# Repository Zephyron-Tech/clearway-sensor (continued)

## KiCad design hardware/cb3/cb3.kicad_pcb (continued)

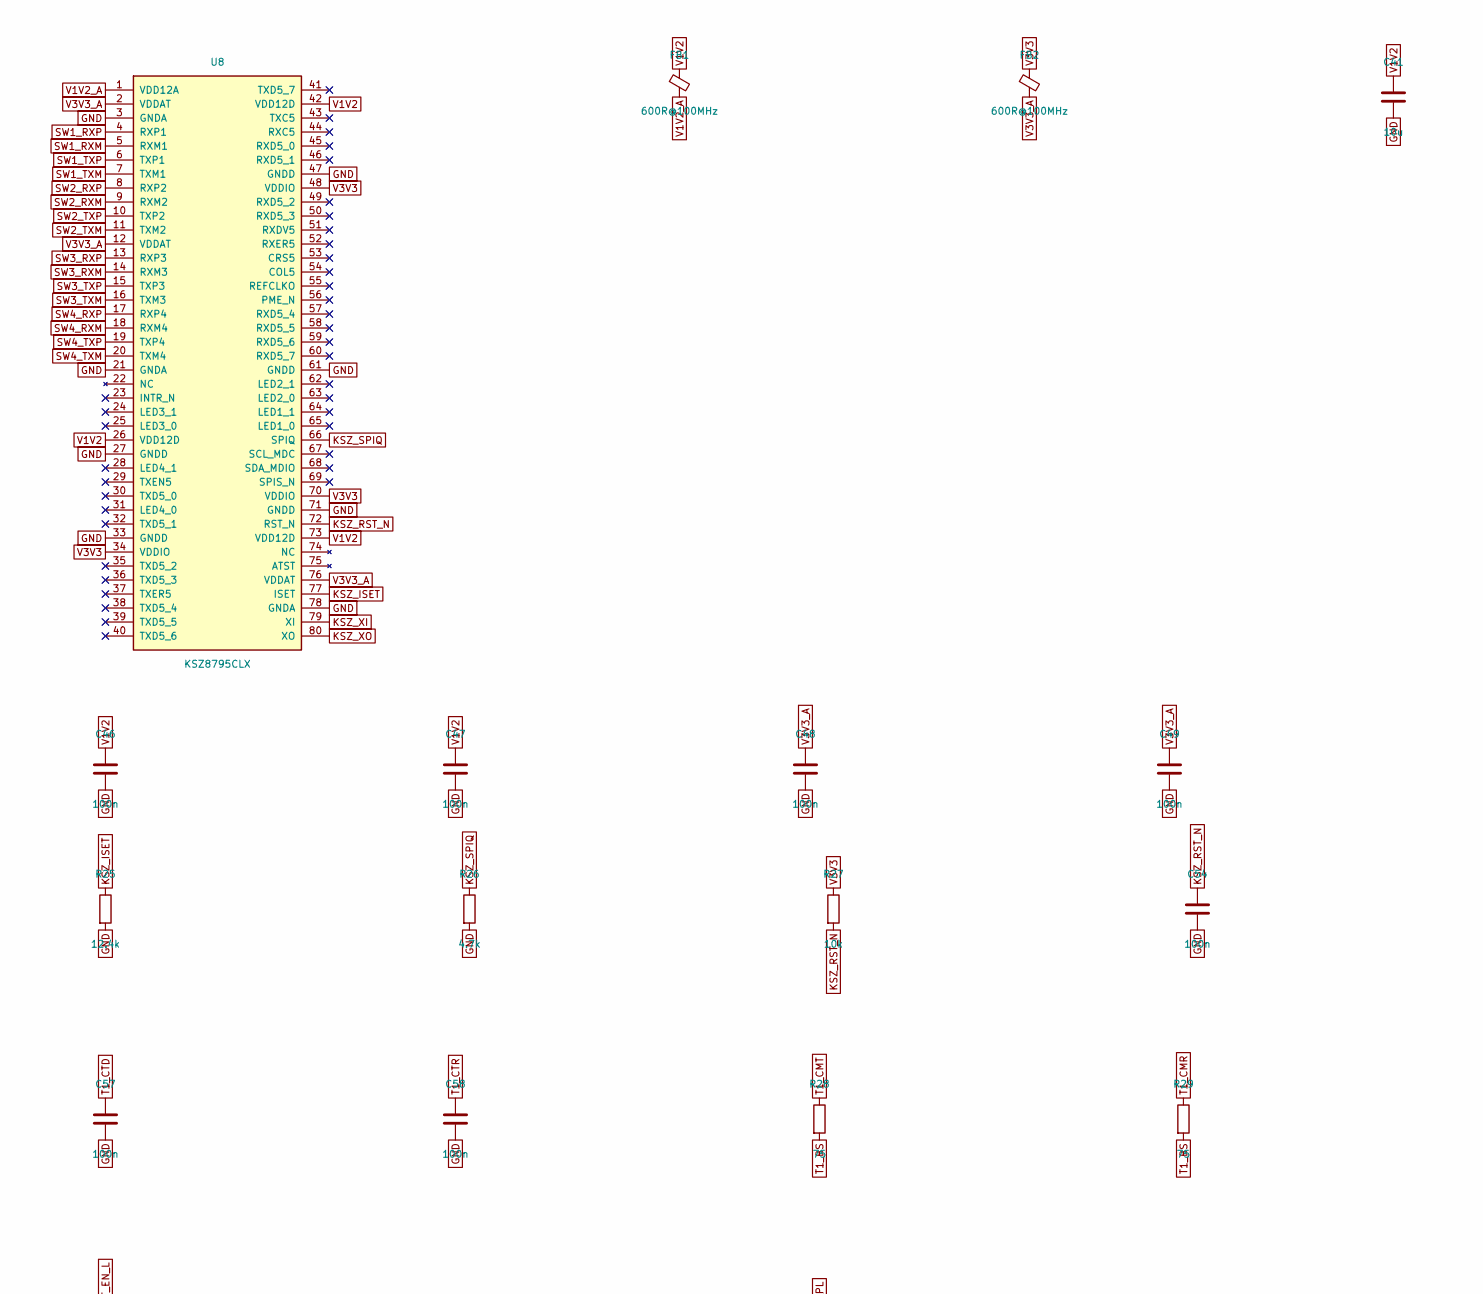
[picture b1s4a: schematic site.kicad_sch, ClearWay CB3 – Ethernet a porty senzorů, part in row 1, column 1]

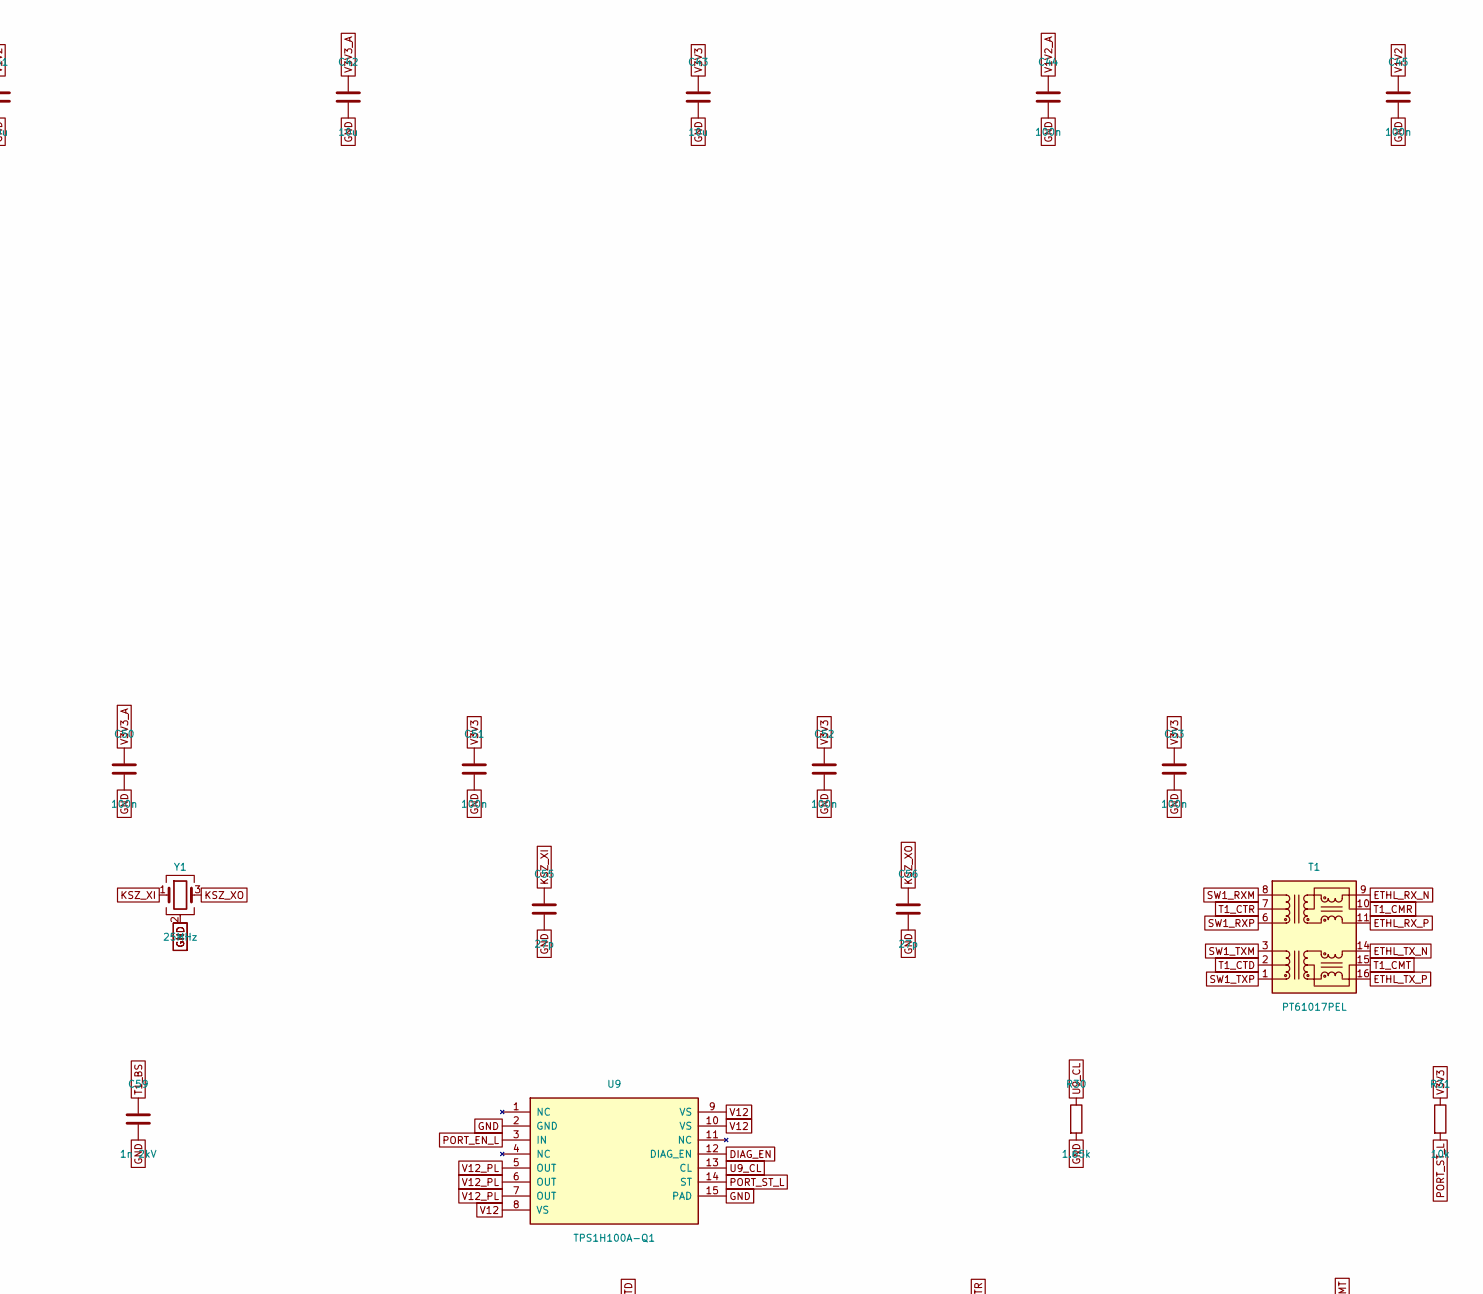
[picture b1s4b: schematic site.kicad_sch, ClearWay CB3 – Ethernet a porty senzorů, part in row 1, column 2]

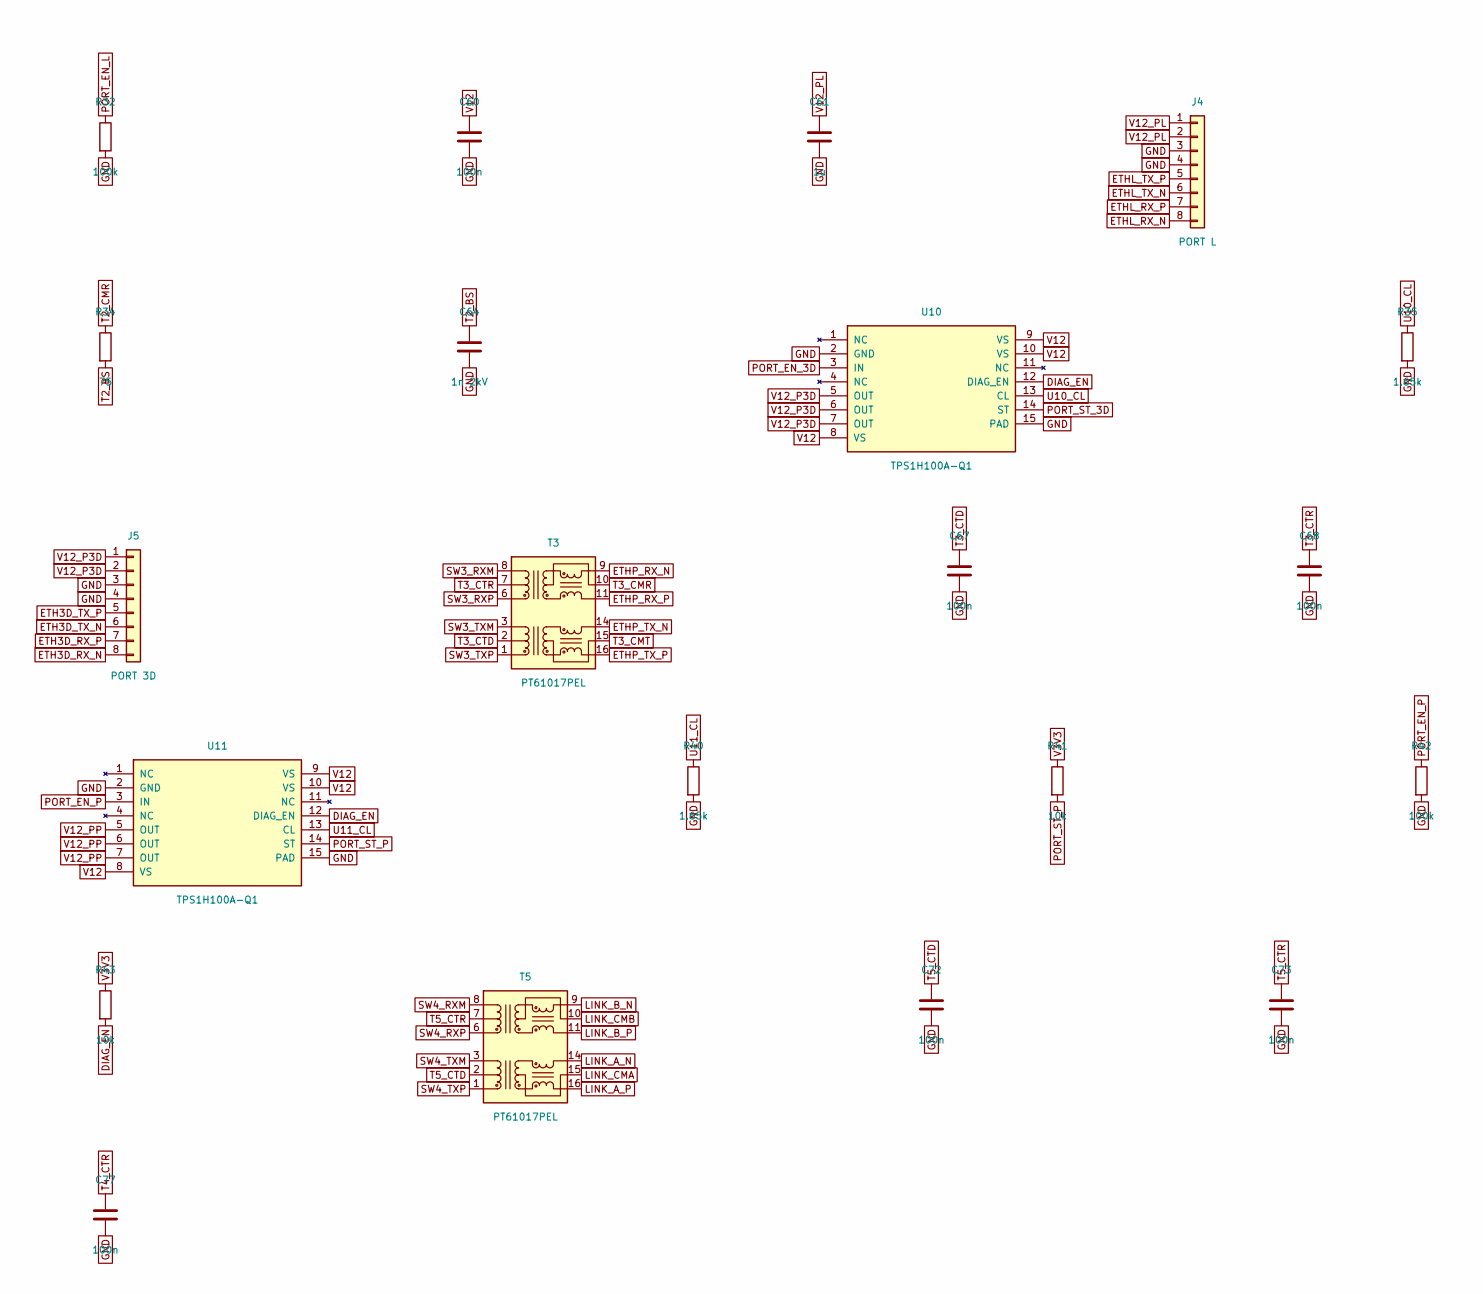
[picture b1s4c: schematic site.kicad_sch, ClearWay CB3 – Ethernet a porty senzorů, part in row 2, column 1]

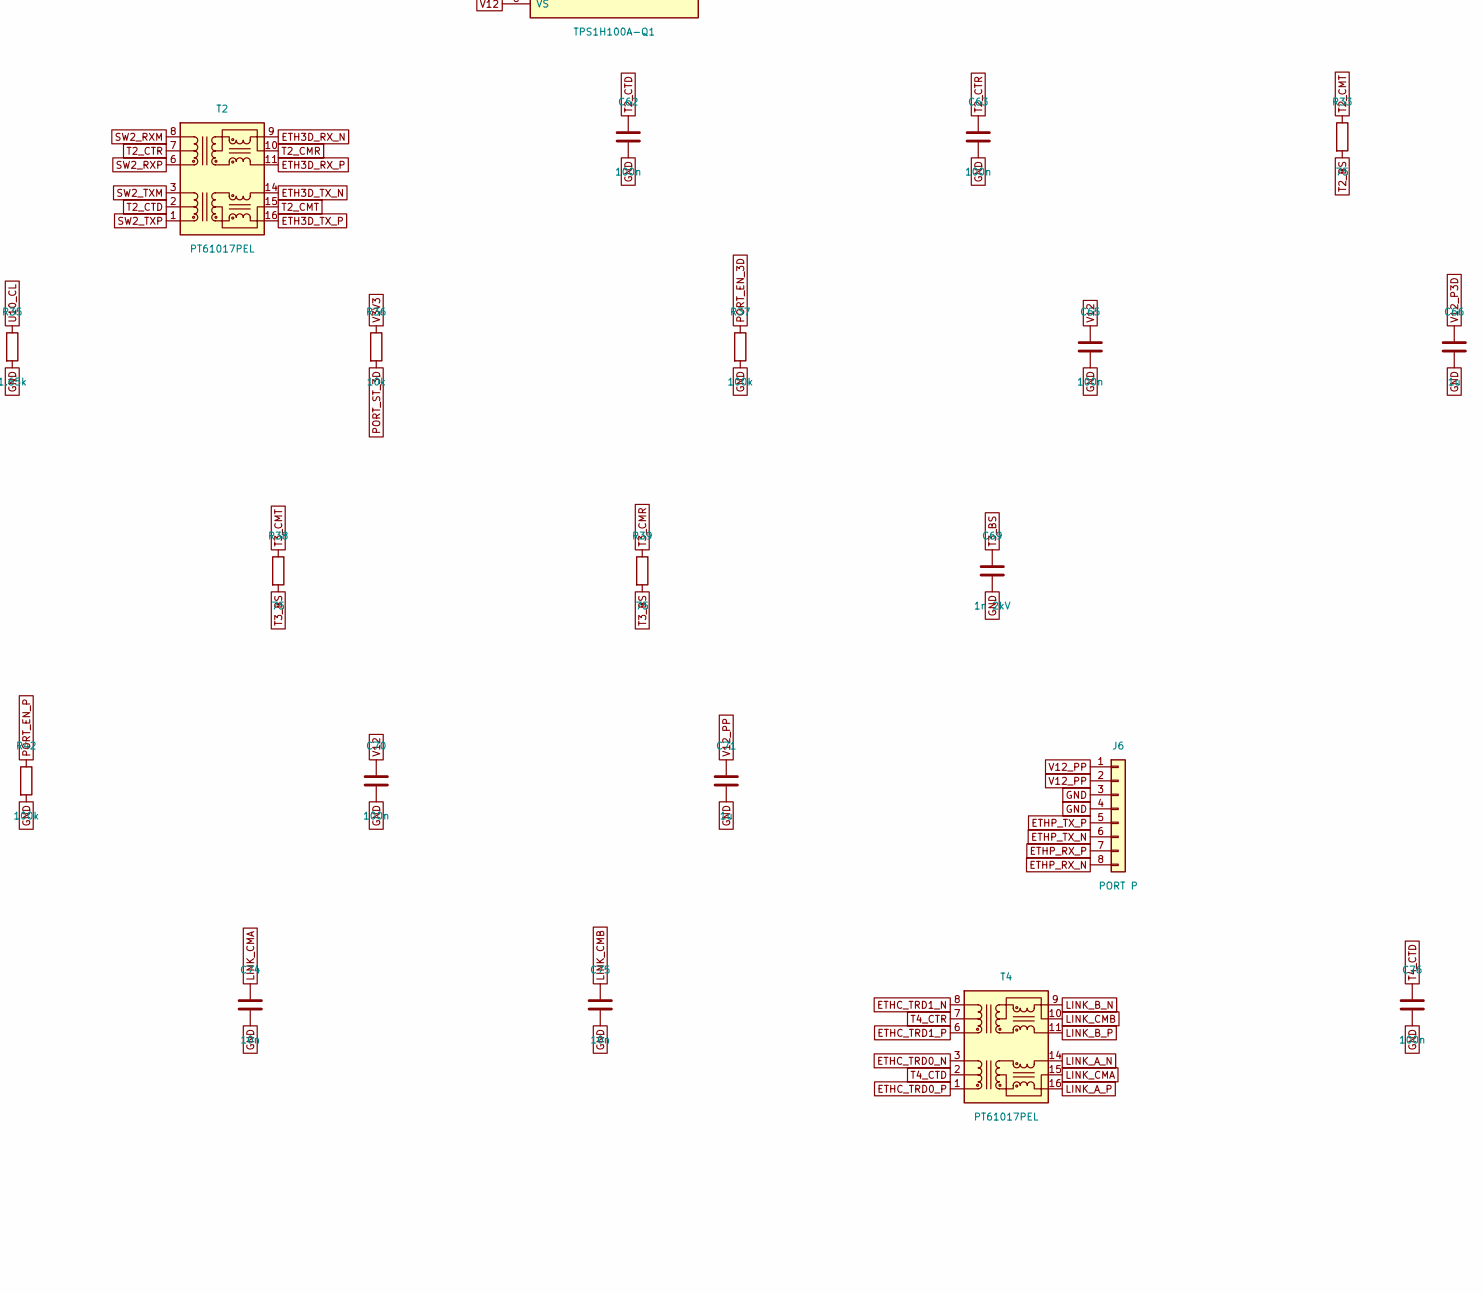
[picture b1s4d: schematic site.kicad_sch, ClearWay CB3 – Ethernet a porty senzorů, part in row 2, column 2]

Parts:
C41, C42, C43: 10u; C_0805_2012Metric; MPN kondenzátor 10 µF 10 V X5R 0805
C44, C45, C46, C47, C48, C49, C50, C51, C52, C53, C54, C57, C58, C62, C63, C67, C68, C72, C73, C76, C77: 100n; C_0402_1005Metric; MPN keramický kondenzátor 100n X7R
C55, C56: 27p; C_0402_1005Metric; MPN kondenzátor 27 pF C0G
C59, C64, C69: 1n 2kV; C_1206_3216Metric; MPN kondenzátor 1 nF 2 kV X7R 1206
C60, C65, C70: 100n; C_0603_1608Metric; MPN kondenzátor 100 nF 50 V X7R 0603
C61, C66, C71: 1u; C_0805_2012Metric; MPN kondenzátor 1 µF 50 V X7R 0805
C74, C75: 10n; C_0402_1005Metric; MPN keramický kondenzátor 10n X7R
FB1, FB2: 600R@100MHz; L_0603_1608Metric; MPN Murata BLM18PG601SN1D
J4: PORT L; JST_GH_SM08B-GHS-TB_1x08-1MP_P1.25mm_Horizontal; MPN JST SM08B-GHS-TB
J5: PORT 3D; JST_GH_SM08B-GHS-TB_1x08-1MP_P1.25mm_Horizontal; MPN JST SM08B-GHS-TB
J6: PORT P; JST_GH_SM08B-GHS-TB_1x08-1MP_P1.25mm_Horizontal; MPN JST SM08B-GHS-TB
R25: 12.4k; R_0402_1005Metric; MPN rezistor 12,4 kΩ 1 % 0402 (ISET)
R26: 4.7k; R_0402_1005Metric; MPN rezistor 4,7 kΩ 0402 (strap: SPI klient)
R27, R31, R36, R41, R43: 10k; R_0402_1005Metric; MPN rezistor 10k 1 % 0402
R28, R29, R33, R34, R38, R39: 75; R_0402_1005Metric; MPN rezistor 75 1 % 0402
R30, R35, R40: 1.65k; R_0402_1005Metric; MPN rezistor 1,65 kΩ 1 % 0402 (omezení prou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
R32, R37, R42: 100k; R_0402_1005Metric; MPN rezistor 100k 1 % 0402
T1, T2, T3, T4, T5: PT61017PEL; Transformer_Ethernet_Bourns_PT61017PEL; MPN Bourns PT61017PEL (10/100, 1:1)
U8: KSZ8795CLX; LQFP-80_12x12mm_P0.5mm; MPN Microchip KSZ8795CLXIC
U9, U10, U11: TPS1H100A-Q1; TSSOP-14-1EP_4.4x5mm_P0.65mm; MPN TI TPS1H100AQPWPRQ1 (verze A, výstup ST)
Y1: 25MHz; Crystal_SMD_3225-4Pin_3.2x2.5mm; MPN Abracon ABM8-25.000MHZ-B2-T (18 pF, ±30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

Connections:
DIAG_EN: R43.2, U9.12 (DIAG_EN), U10.12 (DIAG_EN), U11.12 (DIAG_EN)
ETH3D_RX_N: J5.8, T2.9 (RX-)
ETH3D_RX_P: J5.7, T2.11 (RX+)
ETH3D_TX_N: J5.6, T2.14 (TX-)
ETH3D_TX_P: J5.5, T2.16 (TX+)
ETHC_TRD0_N: T4.3 (TD-); also elsewhere on the board
ETHC_TRD0_P: T4.1 (TD+); also elsewhere on the board
ETHC_TRD1_N: T4.8 (RD-); also elsewhere on the board
ETHC_TRD1_P: T4.6 (RD+); also elsewhere on the board
ETHL_RX_N: J4.8, T1.9 (RX-)
ETHL_RX_P: J4.7, T1.11 (RX+)
ETHL_TX_N: J4.6, T1.14 (TX-)
ETHL_TX_P: J4.5, T1.16 (TX+)
ETHP_RX_N: J6.8, T3.9 (RX-)
ETHP_RX_P: J6.7, T3.11 (RX+)
ETHP_TX_N: J6.6, T3.14 (TX-)
ETHP_TX_P: J6.5, T3.16 (TX+)
GND: C41.2, C42.2, C43.2, C44.2, C45.2, C46.2, C47.2, C48.2, C49.2, C50.2, C51.2, C52.2, C53.2, C54.2, C55.2, C56.2, C57.2, C58.2, C59.2, C60.2, C61.2, C62.2, C63.2, C64.2, C65.2, C66.2, C67.2, C68.2, C69.2, C70.2, C71.2, C72.2, C73.2, C74.2, C75.2, C76.2, C77.2, J4.3, J4.4, J4.MP, J5.3, J5.4, J5.MP, J6.3, J6.4, J6.MP, R25.2, R26.2, R30.2, R32.2, R35.2, R37.2, R40.2, R42.2, U8.3 (GNDA), U8.21 (GNDA), U8.27 (GNDD), U8.33 (GNDD), U8.47 (GNDD), U8.61 (GNDD), U8.71 (GNDD), U8.78 (GNDA), U9.2 (GND), U9.15 (PAD), U10.2 (GND), U10.15 (PAD), U11.2 (GND), U11.15 (PAD), Y1.2 (G), Y1.4 (G); also elsewhere on the board
KSZ_ISET: R25.1, U8.77 (ISET)
KSZ_RST_N: C54.1, R27.2, U8.72 (RST_N); also elsewhere on the board
KSZ_SPIQ: R26.1, U8.66 (SPIQ)
KSZ_XI: C55.1, U8.79 (XI), Y1.1
KSZ_XO: C56.1, U8.80 (XO), Y1.3
LINK_A_N: T4.14 (TX-), T5.14 (TX-)
LINK_A_P: T4.16 (TX+), T5.16 (TX+)
LINK_B_N: T4.9 (RX-), T5.9 (RX-)
LINK_B_P: T4.11 (RX+), T5.11 (RX+)
LINK_CMA: C74.1, T4.15 (C_TX), T5.15 (C_TX)
LINK_CMB: C75.1, T4.10 (C_RX), T5.10 (C_RX)
PORT_EN_3D: R37.1, U10.3 (IN); also elsewhere on the board
PORT_EN_L: R32.1, U9.3 (IN); also elsewhere on the board
PORT_EN_P: R42.1, U11.3 (IN); also elsewhere on the board
PORT_ST_3D: R36.2, U10.14 (ST); also elsewhere on the board
PORT_ST_L: R31.2, U9.14 (ST); also elsewhere on the board
PORT_ST_P: R41.2, U11.14 (ST); also elsewhere on the board
SW1_RXM: T1.8 (RD-), U8.5 (RXM1)
SW1_RXP: T1.6 (RD+), U8.4 (RXP1)
SW1_TXM: T1.3 (TD-), U8.7 (TXM1)
SW1_TXP: T1.1 (TD+), U8.6 (TXP1)
SW2_RXM: T2.8 (RD-), U8.9 (RXM2)
SW2_RXP: T2.6 (RD+), U8.8 (RXP2)
SW2_TXM: T2.3 (TD-), U8.11 (TXM2)
SW2_TXP: T2.1 (TD+), U8.10 (TXP2)
SW3_RXM: T3.8 (RD-), U8.14 (RXM3)
SW3_RXP: T3.6 (RD+), U8.13 (RXP3)
SW3_TXM: T3.3 (TD-), U8.16 (TXM3)
SW3_TXP: T3.1 (TD+), U8.15 (TXP3)
SW4_RXM: T5.8 (RD-), U8.18 (RXM4)
SW4_RXP: T5.6 (RD+), U8.17 (RXP4)
SW4_TXM: T5.3 (TD-), U8.20 (TXM4)
SW4_TXP: T5.1 (TD+), U8.19 (TXP4)
T1_BS: C59.1, R28.2, R29.2
T1_CMR: R29.1, T1.10 (C_RX)
T1_CMT: R28.1, T1.15 (C_TX)
T1_CTD: C57.1, T1.2 (C_TD)
T1_CTR: C58.1, T1.7 (C_RD)
T2_BS: C64.1, R33.2, R34.2
T2_CMR: R34.1, T2.10 (C_RX)
T2_CMT: R33.1, T2.15 (C_TX)
T2_CTD: C62.1, T2.2 (C_TD)
T2_CTR: C63.1, T2.7 (C_RD)
T3_BS: C69.1, R38.2, R39.2
T3_CMR: R39.1, T3.10 (C_RX)
T3_CMT: R38.1, T3.15 (C_TX)
T3_CTD: C67.1, T3.2 (C_TD)
T3_CTR: C68.1, T3.7 (C_RD)
T4_CTD: C76.1, T4.2 (C_TD)
T4_CTR: C77.1, T4.7 (C_RD)
T5_CTD: C72.1, T5.2 (C_TD)
T5_CTR: C73.1, T5.7 (C_RD)
U9_CL: R30.1, U9.13 (CL)
U10_CL: R35.1, U10.13 (CL)
U11_CL: R40.1, U11.13 (CL)
V1V2: C41.1, C45.1, C46.1, C47.1, FB1.1, U8.26 (VDD12D), U8.42 (VDD12D), U8.73 (VDD12D); also elsewhere on the board
V1V2_A: C44.1, FB1.2, U8.1 (VDD12A)
V3V3: C43.1, C51.1, C52.1, C53.1, FB2.1, R27.1, R31.1, R36.1, R41.1, R43.1, U8.34 (VDDIO), U8.48 (VDDIO), U8.70 (VDDIO); also elsewhere on the board
V3V3_A: C42.1, C48.1, C49.1, C50.1, FB2.2, U8.2 (VDDAT), U8.12 (VDDAT), U8.76 (VDDAT)
V12: C60.1, C65.1, C70.1, U9.8 (VS), U9.9 (VS), U9.10 (VS), U10.8 (VS), U10.9 (VS), U10.10 (VS), U11.8 (VS), U11.9 (VS), U11.10 (VS); also elsewhere on the board
V12_P3D: C66.1, J5.1, J5.2, U10.5 (OUT), U10.6 (OUT), U10.7 (OUT)
V12_PL: C61.1, J4.1, J4.2, U9.5 (OUT), U9.6 (OUT), U9.7 (OUT)
V12_PP: C71.1, J6.1, J6.2, U11.5 (OUT), U11.6 (OUT), U11.7 (OUT)

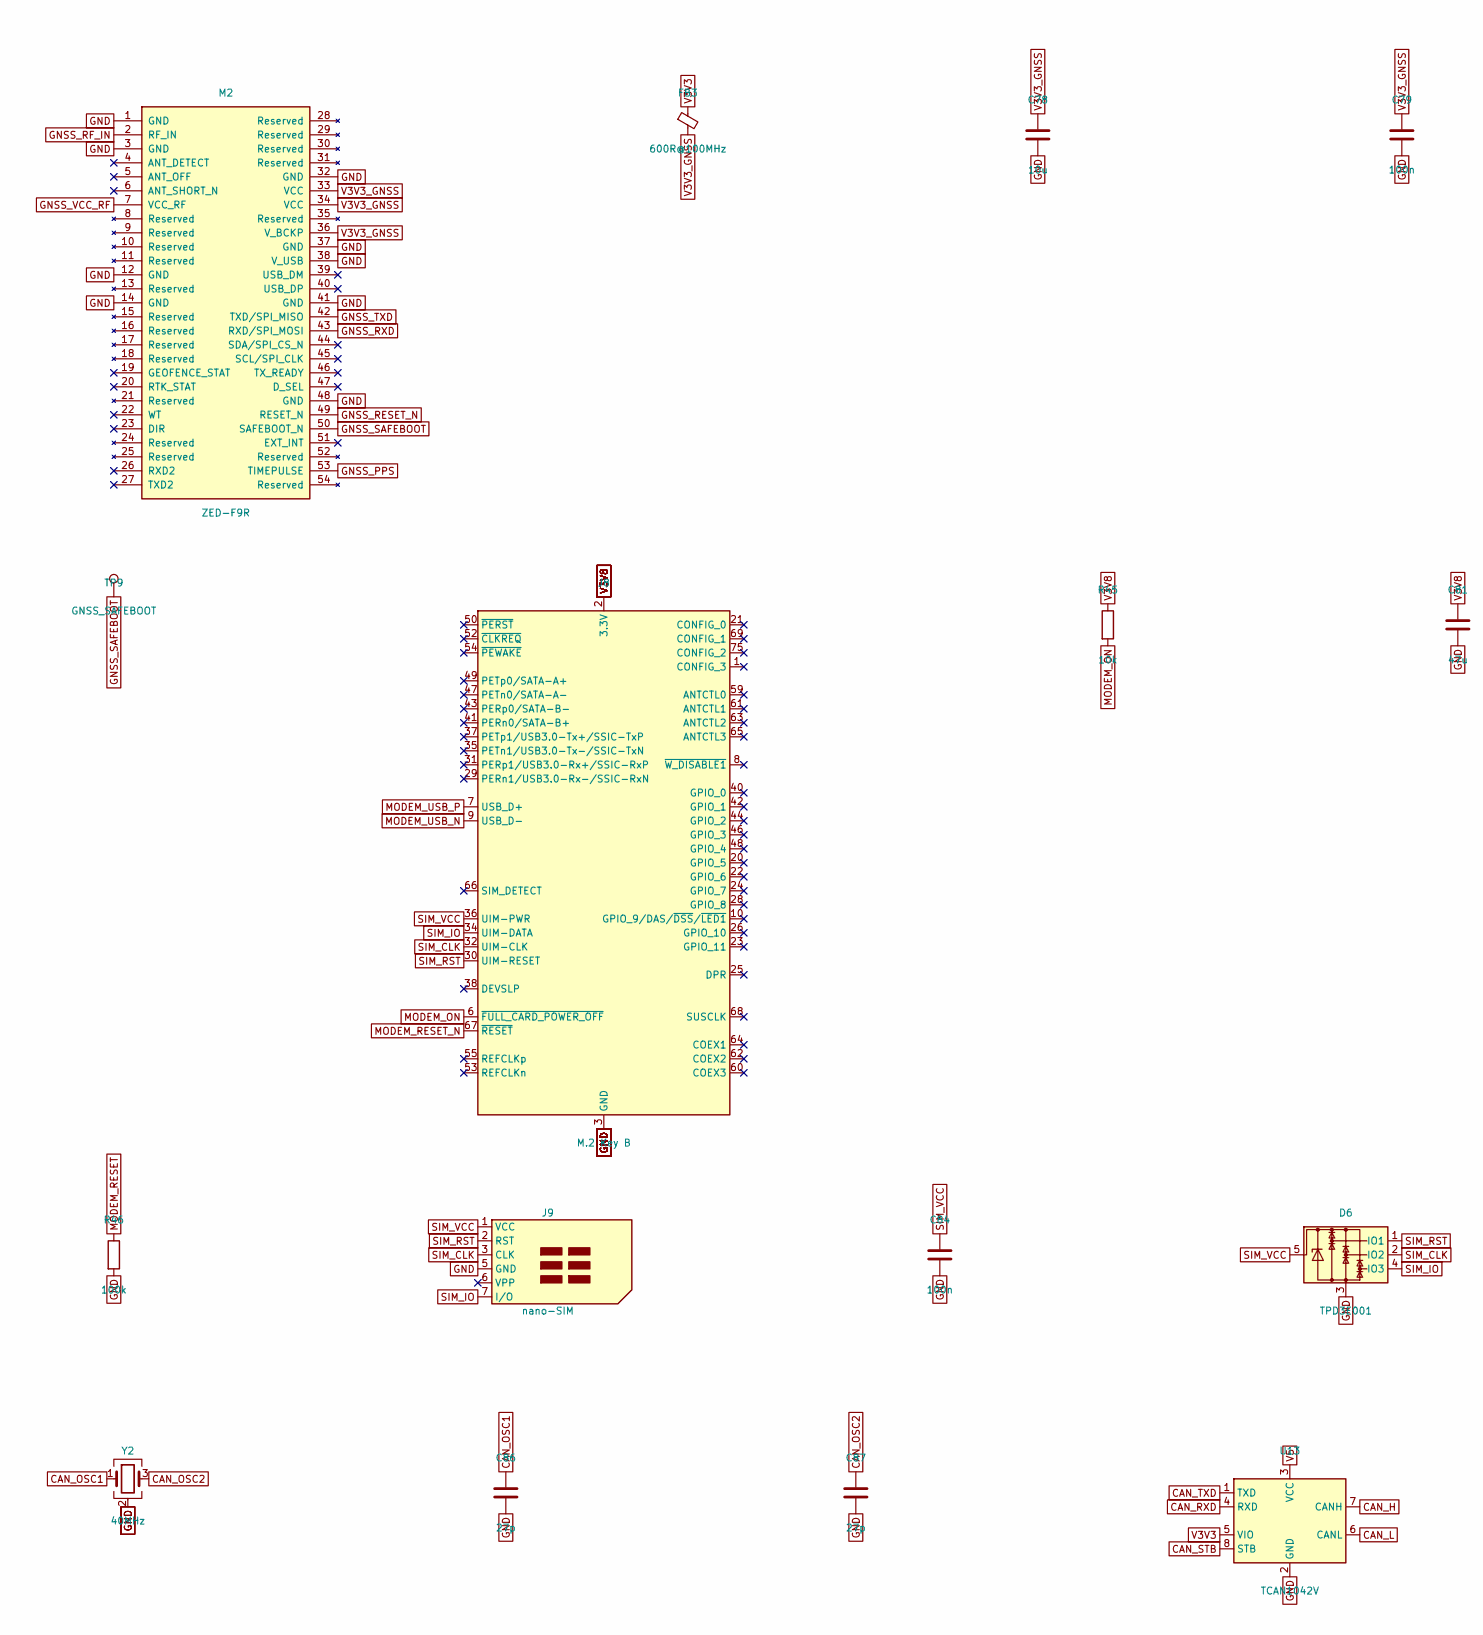
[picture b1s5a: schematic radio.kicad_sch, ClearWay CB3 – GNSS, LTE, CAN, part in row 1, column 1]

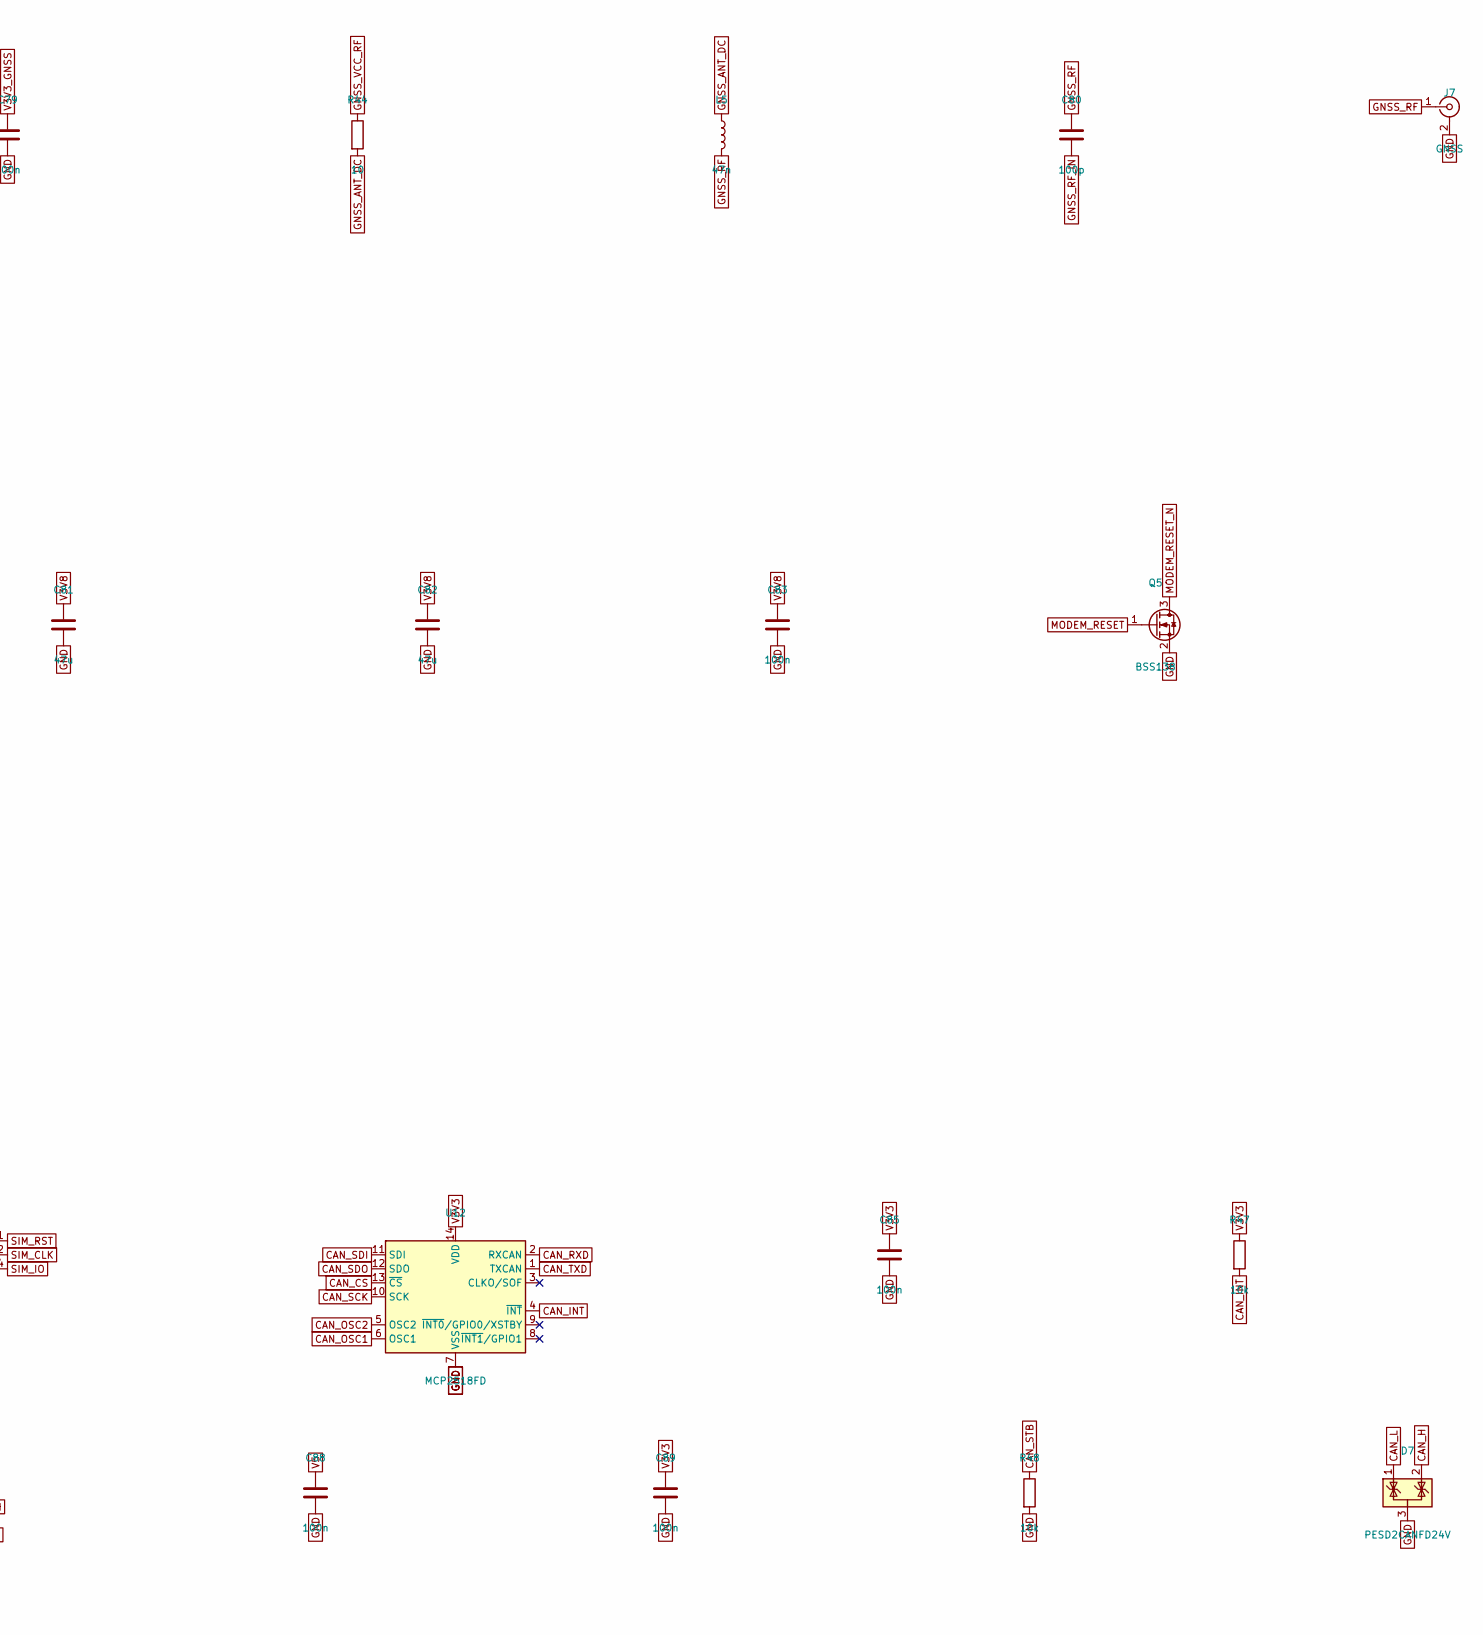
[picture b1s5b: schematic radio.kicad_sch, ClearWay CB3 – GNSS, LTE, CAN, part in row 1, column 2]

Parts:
C78: 10u; C_0805_2012Metric; MPN kondenzátor 10 µF 10 V X5R 0805
C79, C83, C84, C85, C88, C89: 100n; C_0402_1005Metric; MPN keramický kondenzátor 100n X7R
C80: 100p; C_0402_1005Metric; MPN kondenzátor 100 pF C0G 0402 (oddělení D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
C81, C82: 47u; C_1210_3225Metric; MPN kondenzátor 47 µF 10 V X5R 1210
C86, C87: 27p; C_0402_1005Metric; MPN kondenzátor 27 pF C0G
D6: TPD3E001; SOT-553; MPN TI TPD3E001DRLR
D7: PESD2CANFD24V; SOT-23; MPN Nexperia PESD2CANFD24V-T (SOT-23)
FB3: 600R@100MHz; L_0603_1608Metric; MPN Murata BLM18PG601SN1D
J7: GNSS; U.FL_Hirose_U.FL-R-SMT-1_Vertical; MPN Hirose U.FL-R-SMT-1(10)
J8: M.2 Key B; M.2_Socket_KeyB_TopMount_H4.2; MPN TE 2199230-3 (M.2 Key B, 4,2 mm) – ověř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
J9: nano-SIM; nanoSIM_GCT_SIM8060-6-0-14-00; MPN GCT SIM8060-6-0-14-00
L5: 47n; L_0402_1005Metric; MPN Murata LQG15HS47NJ02 (47 nH)
M2: ZED-F9R; ublox_ZED; MPN u-blox ZED-F9R-02B
Q5: BSS138; SOT-23; MPN onsemi BSS138
R44: 10; R_0402_1005Metric; MPN rezistor 10 Ω 0402
R45: 10k; R_0402_1005Metric; MPN rezistor 10 kΩ 0402 (FULL_CARD_POWER_OF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
R46: 100k; R_0402_1005Metric; MPN rezistor 100k 1 % 0402
R47, R48: 10k; R_0402_1005Metric; MPN rezistor 10k 1 % 0402
TP9: GNSS_SAFEBOOT; TestPoint_Pad_D1.5mm; MPN testovací ploška
U12: MCP2518FD; DFN-14-1EP_3x4.5mm_P0.65mm_EP1.65x4.25mm; MPN Microchip MCP2518FDT-E/QBB
U13: TCAN1042V; SOIC-8_3.9x4.9mm_P1.27mm; MPN TI TCAN1042VDRQ1 (pin 5 = VIO)
Y2: 40MHz; Crystal_SMD_3225-4Pin_3.2x2.5mm; MPN Abracon ABM8-40.000MHZ-B2-T (18 pF)

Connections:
CAN_CS: U12.13 (~CS); also elsewhere on the board
CAN_H: D7.2 (K), U13.7 (CANH); also elsewhere on the board
CAN_INT: R47.2, U12.4 (~INT); also elsewhere on the board
CAN_L: D7.1 (K), U13.6 (CANL); also elsewhere on the board
CAN_OSC1: C86.1, U12.6 (OSC1), Y2.1
CAN_OSC2: C87.1, U12.5 (OSC2), Y2.3
CAN_RXD: U12.2 (RXCAN), U13.4 (RXD)
CAN_SCK: U12.10 (SCK); also elsewhere on the board
CAN_SDI: U12.11 (SDI); also elsewhere on the board
CAN_SDO: U12.12 (SDO); also elsewhere on the board
CAN_STB: R48.1, U13.8 (STB); also elsewhere on the board
CAN_TXD: U12.1 (TXCAN), U13.1 (TXD)
GND: C78.2, C79.2, C81.2, C82.2, C83.2, C84.2, C85.2, C86.2, C87.2, C88.2, C89.2, D6.3, D7.3 (A), J7.2 (Ext), J8.3 (GND), J8.5 (GND), J8.11 (GND), J8.27 (GND), J8.33 (GND), J8.39 (GND), J8.45 (GND), J8.51 (GND), J8.57 (GND), J8.71 (GND), J8.73 (GND), J8.M2, J8.S1, J8.S2, J9.5 (GND), J9.SH, M2.1 (GND), M2.3 (GND), M2.12 (GND), M2.14 (GND), M2.32 (GND), M2.37 (GND), M2.38 (V_USB), M2.41 (GND), M2.48 (GND), Q5.2 (S), R46.2, R48.2, U12.7 (VSS), U12.15 (VSS), U13.2 (GND), Y2.2 (G), Y2.4 (G); also elsewhere on the board
GNSS_ANT_DC: L5.1, R44.2
GNSS_PPS: M2.53 (TIMEPULSE); also elsewhere on the board
GNSS_RESET_N: M2.49 (RESET_N); also elsewhere on the board
GNSS_RF: C80.1, J7.1 (In), L5.2
GNSS_RF_IN: C80.2, M2.2 (RF_IN)
GNSS_RXD: M2.43 (RXD/SPI_MOSI); also elsewhere on the board
GNSS_SAFEBOOT: M2.50 (SAFEBOOT_N), TP9.1
GNSS_TXD: M2.42 (TXD/SPI_MISO); also elsewhere on the board
GNSS_VCC_RF: M2.7 (VCC_RF), R44.1
MODEM_ON: J8.6 (~FULL_CARD_POWER_OFF), R45.2
MODEM_RESET: Q5.1 (G), R46.1; also elsewhere on the board
MODEM_RESET_N: J8.67 (~RESET), Q5.3 (D)
MODEM_USB_N: J8.9 (USB_D-); also elsewhere on the board
MODEM_USB_P: J8.7 (USB_D+); also elsewhere on the board
SIM_CLK: D6.2 (IO2), J8.32 (UIM-CLK), J9.3 (CLK)
SIM_IO: D6.4 (IO3), J8.34 (UIM-DATA), J9.7 (I/O)
SIM_RST: D6.1 (IO1), J8.30 (UIM-RESET), J9.2 (RST)
SIM_VCC: C84.1, D6.5, J8.36 (UIM-PWR), J9.1 (VCC)
V3V3: C85.1, C89.1, FB3.1, R47.1, U12.14 (VDD), U13.5 (VIO); also elsewhere on the board
V3V3_GNSS: C78.1, C79.1, FB3.2, M2.33 (VCC), M2.34 (VCC), M2.36 (V_BCKP)
V3V8: C81.1, C82.1, C83.1, J8.2 (3.3V), J8.4 (3.3V), J8.70 (3.3V), J8.72 (3.3V), J8.74 (3.3V), R45.1; also elsewhere on the board
V5: C88.1, U13.3 (VCC); also elsewhere on the board

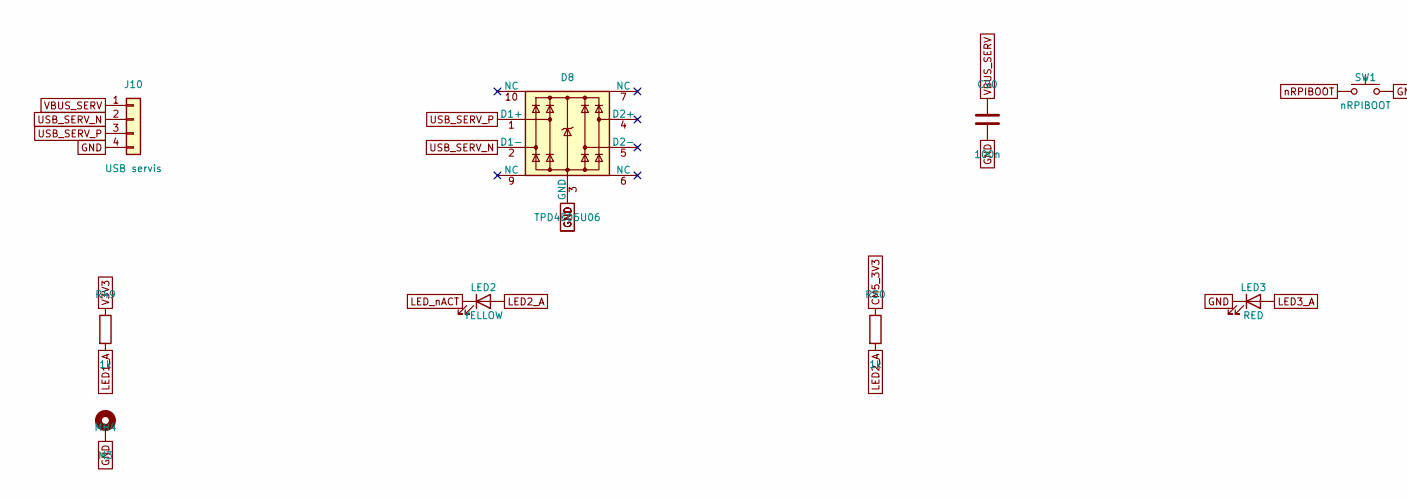
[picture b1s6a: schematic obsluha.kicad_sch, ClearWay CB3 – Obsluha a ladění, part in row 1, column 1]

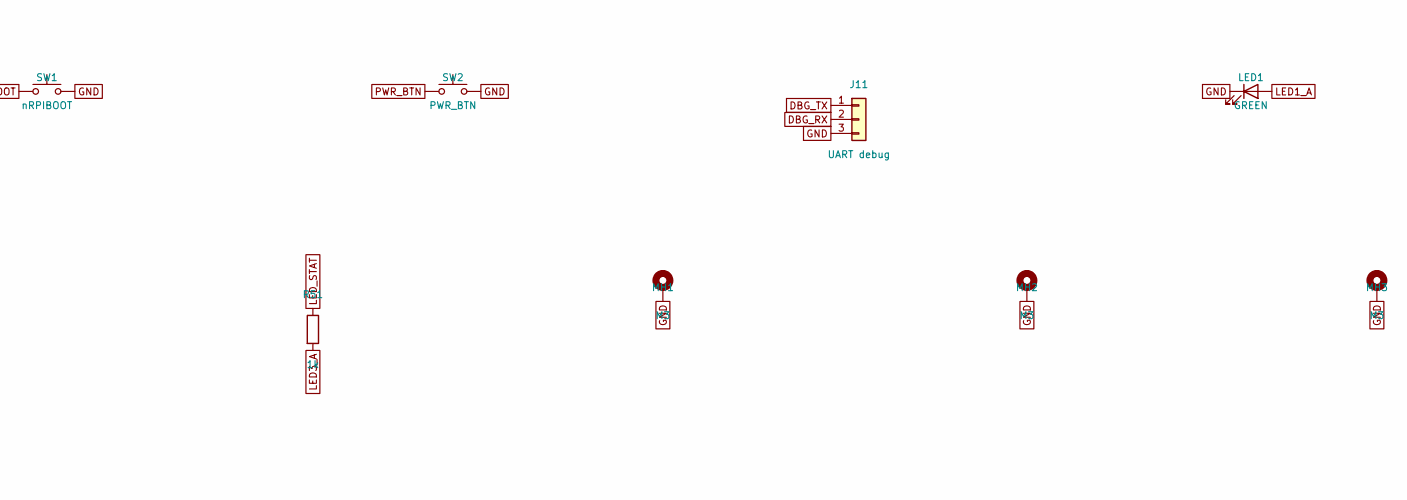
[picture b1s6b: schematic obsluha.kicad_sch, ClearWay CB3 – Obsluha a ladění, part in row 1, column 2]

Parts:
C90: 100n; C_0402_1005Metric; MPN keramický kondenzátor 100n X7R
D8: TPD4E05U06; USON-10_2.5x1.0mm_P0.5mm; MPN TI TPD4E05U06DQAR
J10: USB servis; JST_GH_SM04B-GHS-TB_1x04-1MP_P1.25mm_Horizontal; MPN JST SM04B-GHS-TB
J11: UART debug; JST_GH_SM03B-GHS-TB_1x03-1MP_P1.25mm_Horizontal; MPN JST SM03B-GHS-TB
LED1: GREEN; LED_0603_1608Metric; MPN Würth 150060VS75000
LED2: YELLOW; LED_0603_1608Metric; MPN Würth 150060YS75000
LED3: RED; LED_0603_1608Metric; MPN Würth 150060RS75000
MH1, MH2, MH3, MH4: M3; MountingHole_3.2mm_M3_Pad_Via; MPN otvor M3
R49, R50, R51: 1k; R_0402_1005Metric; MPN rezistor 1k 1 % 0402
SW1: nRPIBOOT; SW_Push_1P1T_NO_CK_KMR2; MPN C&K KMR221GLFS
SW2: PWR_BTN; SW_Push_1P1T_NO_CK_KMR2; MPN C&K KMR221GLFS

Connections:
CM5_3V3: R50.1; also elsewhere on the board
DBG_RX: J11.2; also elsewhere on the board
DBG_TX: J11.1; also elsewhere on the board
GND: C90.2, D8.3 (GND), D8.8 (GND), J10.4, J10.MP, J11.3, J11.MP, LED1.1 (K), LED3.1 (K), MH1.1, MH2.1, MH3.1, MH4.1, SW1.2, SW2.2; also elsewhere on the board
LED1_A: LED1.2 (A), R49.2
LED2_A: LED2.2 (A), R50.2
LED3_A: LED3.2 (A), R51.2
LED_STAT: R51.1; also elsewhere on the board
LED_nACT: LED2.1 (K); also elsewhere on the board
PWR_BTN: SW2.1; also elsewhere on the board
USB_SERV_N: D8.2 (D1-), J10.2; also elsewhere on the board
USB_SERV_P: D8.1 (D1+), J10.3; also elsewhere on the board
V3V3: R49.1; also elsewhere on the board
VBUS_SERV: C90.1, J10.1
nRPIBOOT: SW1.1; also elsewhere on the board
